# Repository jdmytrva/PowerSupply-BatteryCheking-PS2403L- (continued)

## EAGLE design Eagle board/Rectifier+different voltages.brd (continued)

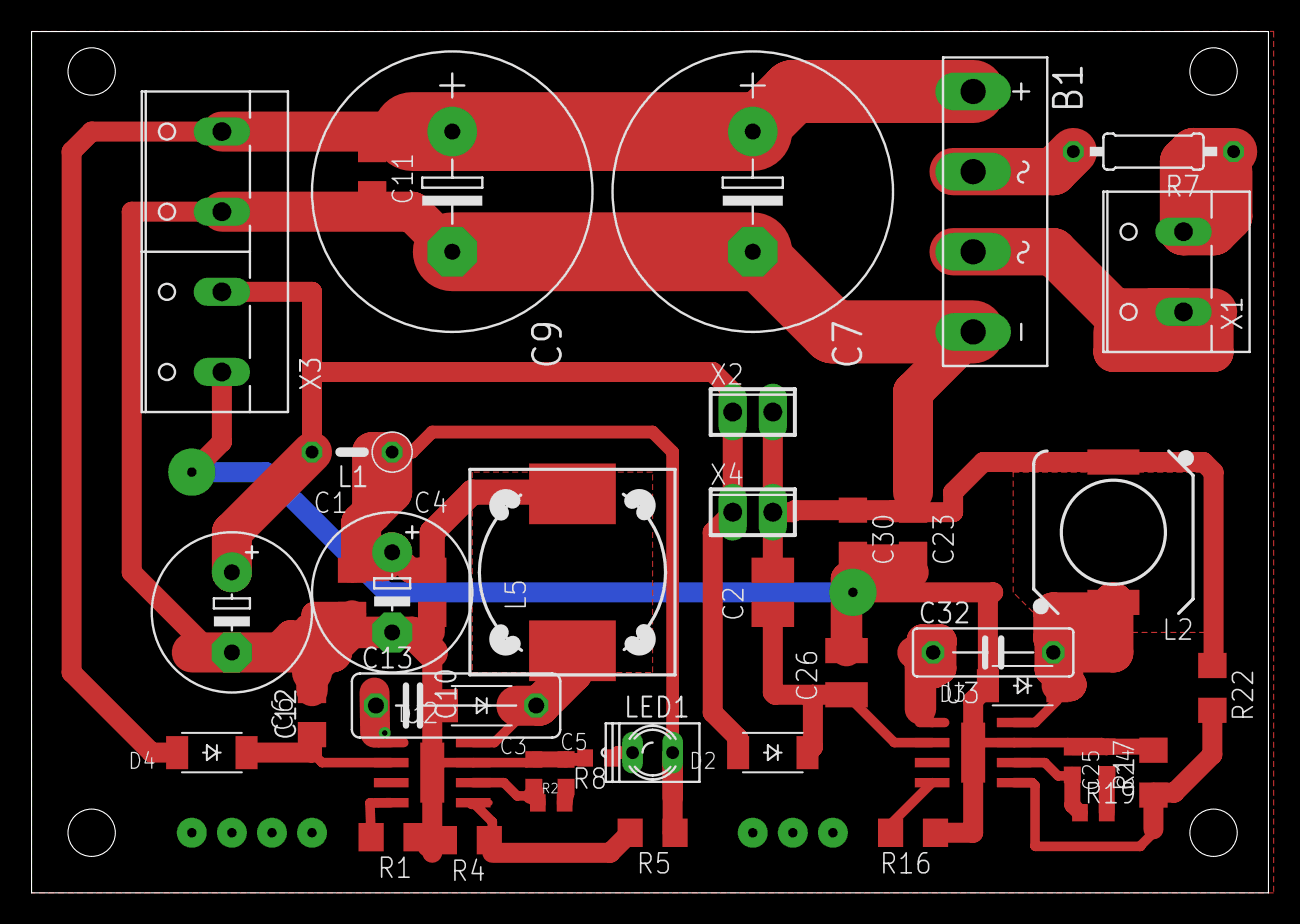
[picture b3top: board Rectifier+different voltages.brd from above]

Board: 2 copper layers, 78.4 x 54.6 mm, 43 parts (0 on the bottom side), 23 nets.

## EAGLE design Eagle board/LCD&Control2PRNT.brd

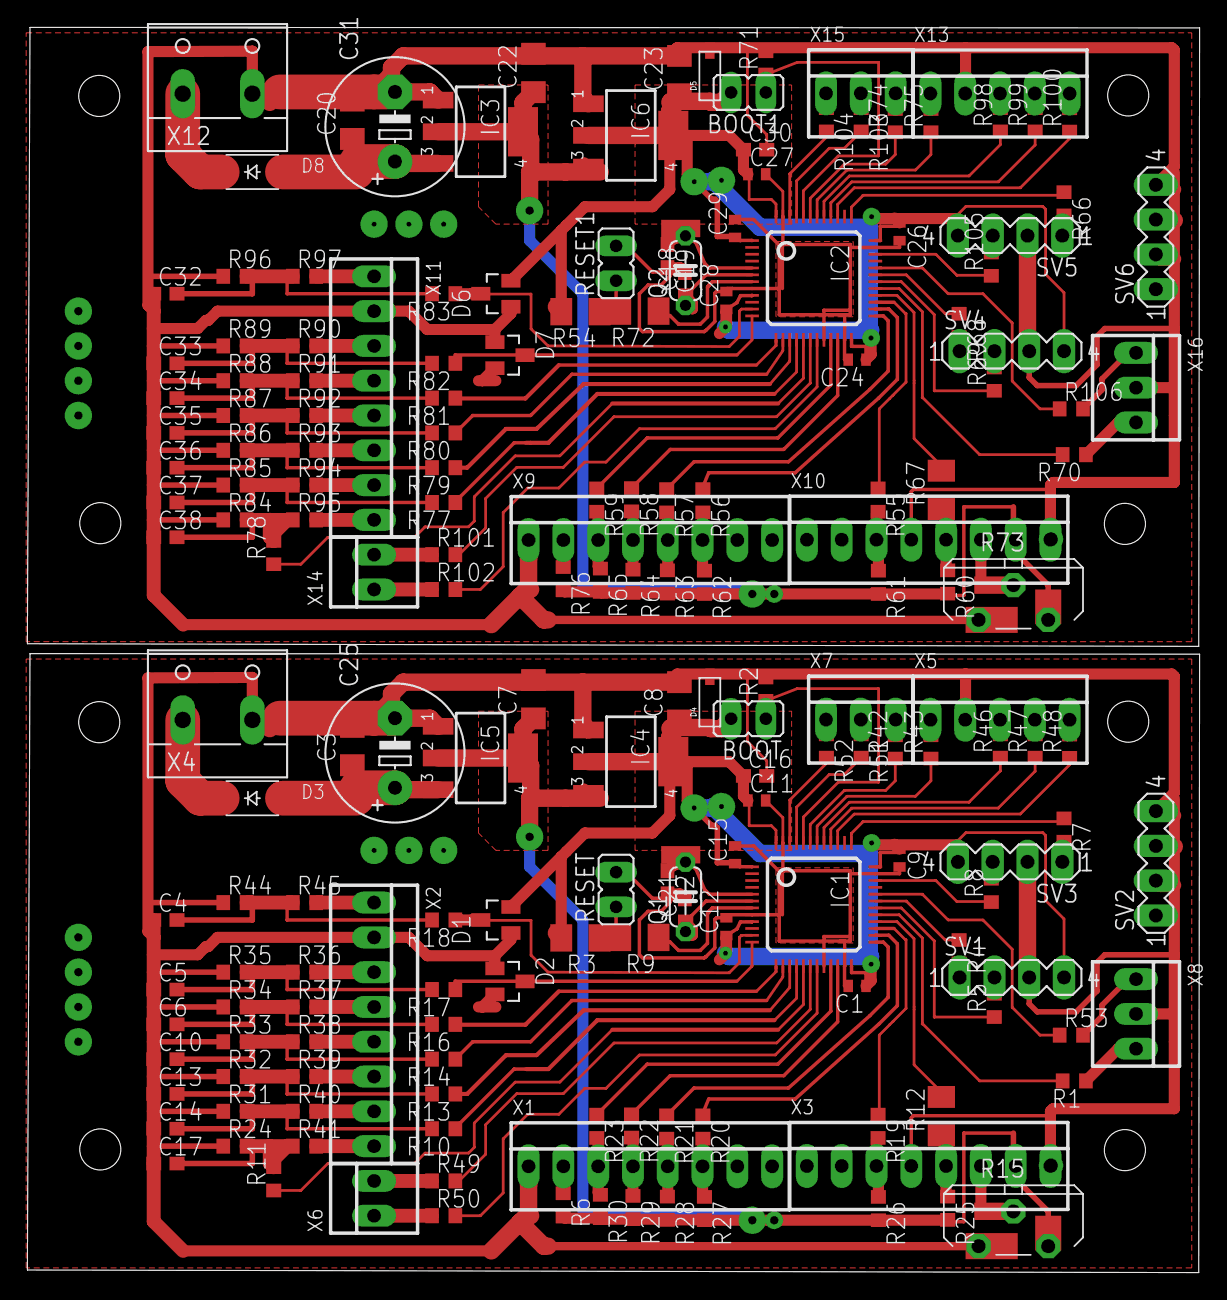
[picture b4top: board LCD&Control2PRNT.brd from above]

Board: 2 copper layers, 85.6 x 90.9 mm, 186 parts (0 on the bottom side), 150 nets.

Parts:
BOOT, BOOT1: JP1
C1, C9, C11, C12, C15, C24, C26, C27, C28, C29: 0.1; C0402
C2, C18, C19, C21: 22p; C0603
C3, C7, C8, C20, C22, C23: 0.1; C1206
C4, C5, C6, C10, C13, C14, C17, C32, C33, C34, C35, C36, C37, C38: C0603
C16, C30: 1uF; C0603
C25, C31: 470uF; E5-10,5
D1, D2, D6, D7: BAT54S; SOT23
D3, D8: PMEG4050EP; SOD128
D4, D5: 3.6v; SOD-123
IC1, IC2: STM32F10XCXT6; TQFP48
IC3, IC5: 5V; SOT223
IC4, IC6: 3.3V; SOT223
Q1, Q2: 8 Mgz; C050-024X044
R1, R4, R5, R7, R8, R10, R11, R13, R14, R16, R17, R18, R19, R24, R31, R32, R33, R34, R35, R36, R37, R38, R39, R40, R41, R42, R43, R44, R45, R46, R47, R48, R49, R50, R51, R52, R53, R55, R66, R68, R69, R70, R74, R75, R77, R78, R79, R80, R81, R82, R83, R84, R85, R86, R87, R88, R89, R90, R91, R92, R93, R94, R95, R96, R97, R98, R99, R100, R101, R102, R103, R104, R105, R106: 200; R0603
R2, R25, R26, R27, R28, R29, R30, R60, R61, R62, R63, R64, R65, R71: 10k; R0603
R3, R54: 10k; M1206
R6, R76: 470; R0603
R9, R72: 0; M1206
R12, R67: 200; M1206
R15, R73: PT-10S
R20, R21, R22, R56, R57, R58: R0603
R23, R59: 220; R0603
RESET, RESET1: JP1
SV1, SV2, SV3, SV4, SV5, SV6: MA04-1
X1, X2, X3, X9, X10, X11: 22-23-2081
X4, X12: W237-132
X5, X13: 22-23-2051
X6, X14: 22-23-2021
X7, X8, X15, X16: 22-23-2031

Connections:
+3V1: BOOT1.2, C23.1, C24.1, C26.1, C27.1, C28.1, C29.1, C30.1, D5.C, D6.2, D7.2, IC2.1, IC2.9, IC2.24, IC2.36, IC2.48, IC6.2, IC6.4, R54.2, SV4.4, SV5.4
+3V3: BOOT.2, C1.1, C8.1, C9.1, C11.1, C12.1, C15.1, C16.1, D1.2, D2.2, D4.C, IC1.1, IC1.9, IC1.24, IC1.36, IC1.48, IC4.2, IC4.4, R3.2, SV1.4, SV3.4
+5V: C7.1, IC4.3, IC5.2, IC5.4, R6.2, R15.2, R25.2, R26.2, R27.2, R28.2, R29.2, R30.2, X3.7
+5V1: C22.1, IC3.2, IC3.4, IC6.3, R60.2, R61.2, R62.2, R63.2, R64.2, R65.2, R73.2, R76.2, X10.7
+12V: C3.1, C25.+, D3.2, IC5.3
+12V1: C20.1, C31.+, D8.2, IC3.3
GND: C1.2, C2.2, C3.2, C4.1, C5.1, C6.1, C7.2, C8.2, C9.2, C10.1, C11.2, C12.2, C13.1, C14.1, C15.2, C16.2, C17.1, C21.2, C25.-, D1.1, D2.1, D4.A, IC1.8, IC1.20, IC1.23, IC1.35, IC1.47, IC4.1, IC5.1, R2.2, R15.1, R24.1, R31.1, R32.1, R33.1, R34.1, R35.1, R44.1, RESET.2, SV1.3, SV2.2, SV2.3, SV2.4, SV3.2, X1.1, X2.2, X3.4, X3.8, X4.2, X5.2, X8.2
GND1: C18.2, C19.2, C20.2, C22.2, C23.2, C24.2, C26.2, C27.2, C28.2, C29.2, C30.2, C31.-, C32.1, C33.1, C34.1, C35.1, C36.1, C37.1, C38.1, D5.A, D6.1, D7.1, IC2.8, IC2.20, IC2.23, IC2.35, IC2.47, IC3.1, IC6.1, R71.2, R73.1, R84.1, R85.1, R86.1, R87.1, R88.1, R89.1, R96.1, RESET1.2, SV4.3, SV5.2, SV6.2, SV6.3, SV6.4, X9.1, X10.4, X10.8, X11.2, X12.2, X13.2, X16.2
unnamed: IC1.29, R1.2
unnamed: C21.1, IC1.6, Q1.1
unnamed: C2.1, IC1.5, Q1.2
unnamed: IC1.37, R7.1
unnamed: IC1.34, R8.1
unnamed: R7.2, SV3.1
unnamed: R3.1, R9.2, RESET.1
unnamed: IC1.7, R9.1
unnamed: IC1.31, R4.1
unnamed: IC1.30, R5.1
unnamed: R4.2, SV1.1
unnamed: R6.1, X1.2
unnamed: R15.3, X3.6
unnamed: D3.1, X4.1
unnamed: R22.2, R29.1, X1.4
unnamed: C17.2, R11.2, R24.2, R41.1
unnamed: R52.1, X7.1
unnamed: R1.1, X8.3
unnamed: IC1.46, R52.2
unnamed: R43.2, X5.1
unnamed: R21.2, R28.1, X1.5
unnamed: D1.3, IC1.11, R18.1
unnamed: R20.2, R27.1, X1.6
unnamed: R19.2, R26.1, X3.3
unnamed: R23.2, R30.1, X1.3
unnamed: R12.1, R25.1, X3.5
unnamed: IC1.21, R23.1
unnamed: IC1.22, R22.1
unnamed: IC1.25, R21.1
unnamed: IC1.45, R51.2
unnamed: R47.2, X5.4
unnamed: R5.2, SV1.2
unnamed: R46.2, X5.3
unnamed: R48.2, X5.5
unnamed: R51.1, X7.2
unnamed: R8.2, SV3.3
unnamed: IC1.18, R49.2
unnamed: IC1.43, R42.1
unnamed: D2.3, IC1.12, R17.1
unnamed: BOOT.1, IC1.44, R2.1
unnamed: R42.2, X7.3
unnamed: IC1.42, R43.1
unnamed: C14.2, R10.2, R31.2, R40.1
unnamed: C13.2, R13.2, R32.2, R39.1
unnamed: R38.2, X2.5
unnamed: IC1.13, R16.1
unnamed: IC1.19, R50.2
unnamed: IC1.14, R14.1
unnamed: C6.2, R16.2, R34.2, R37.1
unnamed: C5.2, R17.2, R35.2, R36.1
unnamed: IC1.26, R20.1
unnamed: IC1.27, R19.1
unnamed: IC1.28, R12.2
unnamed: R49.1, X6.2
unnamed: IC1.15, R13.1
unnamed: IC1.16, R10.1
unnamed: R45.2, X2.1
unnamed: IC1.41, R46.1
unnamed: IC1.17, R11.1
unnamed: R50.1, X6.1
unnamed: IC1.40, R47.1
unnamed: IC1.39, R48.1
unnamed: C4.2, R18.2, R44.2, R45.1
unnamed: R36.2, X2.3
unnamed: R37.2, X2.4
unnamed: R53.2, X8.1
unnamed: IC1.32, R53.1
unnamed: C10.2, R14.2, R33.2, R38.1
unnamed: R39.2, X2.6
unnamed: C18.1, IC2.6, Q2.1
unnamed: C19.1, IC2.5, Q2.2
unnamed: R59.2, R65.1, X9.3
unnamed: R40.2, X2.7
unnamed: BOOT1.1, IC2.44, R71.1
unnamed: R58.2, R64.1, X9.4
unnamed: R57.2, R63.1, X9.5
unnamed: R56.2, R62.1, X9.6
unnamed: R55.2, R61.1, X10.3
unnamed: R60.1, R67.1, X10.5
unnamed: IC2.21, R59.1
unnamed: R41.2, X2.8
unnamed: IC2.22, R58.1
unnamed: IC2.25, R57.1
unnamed: IC2.26, R56.1
unnamed: IC2.27, R55.1
unnamed: IC2.28, R67.2
unnamed: IC2.34, R105.1
unnamed: IC2.31, R68.1
unnamed: IC2.30, R69.1
unnamed: R68.2, SV4.1
unnamed: R69.2, SV4.2
unnamed: R66.2, SV5.1
unnamed: IC2.37, R66.1
unnamed: R105.2, SV5.3
unnamed: R54.1, R72.2, RESET1.1
unnamed: R76.1, X9.2
unnamed: IC2.29, R70.2
unnamed: IC2.7, R72.1
unnamed: R73.3, X10.6
unnamed: D6.3, IC2.11, R83.1
unnamed: D7.3, IC2.12, R82.1
unnamed: IC2.13, R81.1
unnamed: IC2.14, R80.1
unnamed: IC2.15, R79.1
unnamed: IC2.16, R77.1
unnamed: IC2.17, R78.1
unnamed: C38.2, R78.2, R84.2, R95.1
unnamed: C37.2, R77.2, R85.2, R94.1
unnamed: C36.2, R79.2, R86.2, R93.1
unnamed: R92.2, X11.5
unnamed: C34.2, R81.2, R88.2, R91.1
unnamed: C33.2, R82.2, R89.2, R90.1
unnamed: R97.2, X11.1
unnamed: C32.2, R83.2, R96.2, R97.1
unnamed: R90.2, X11.3
unnamed: R91.2, X11.4
unnamed: C35.2, R80.2, R87.2, R92.1
unnamed: R93.2, X11.6
unnamed: R94.2, X11.7
unnamed: R95.2, X11.8
unnamed: D8.1, X12.1
unnamed: R98.2, X13.3
unnamed: R99.2, X13.4
unnamed: R100.2, X13.5
unnamed: IC2.43, R74.1
unnamed: IC2.42, R75.1
unnamed: IC2.41, R98.1
unnamed: IC2.40, R99.1
unnamed: IC2.39, R100.1
unnamed: IC2.18, R101.2
unnamed: IC2.19, R102.2
unnamed: R101.1, X14.2
unnamed: R102.1, X14.1
unnamed: IC2.46, R104.2
unnamed: IC2.45, R103.2
unnamed: IC2.32, R106.1
unnamed: R75.2, X13.1
unnamed: R104.1, X15.1
unnamed: R103.1, X15.2
unnamed: R74.2, X15.3
unnamed: R70.1, X16.3
unnamed: R106.2, X16.1

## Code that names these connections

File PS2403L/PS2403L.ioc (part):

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Mcu.Name=STM32F100C(8-B)Tx
Mcu.Package=LQFP48
Mcu.UserName=STM32F100C8Tx
PA1.Signal=ADCx_IN1
PA10.Mode=Asynchronous
PA10.Signal=USART1_RX
PA11.Signal=GPIO_Output
PA13.Mode=Serial_Wire
PA13.Signal=SYS_JTMS-SWDIO
PA14.Mode=Serial_Wire
PA14.Signal=SYS_JTCK-SWCLK
PA15.Signal=GPIO_Output
PA2.Signal=ADCx_IN2
PA3.Signal=ADCx_IN3
PA4.Signal=ADCx_IN4
PA5.Signal=ADCx_IN5
PA6.Signal=ADCx_IN6
PA8.Signal=GPIO_Output
PA9.Mode=Asynchronous
PA9.Signal=USART1_TX
PB0.Signal=GPIO_Output
PB1.Signal=GPIO_Output
PB10.GPIOParameters=GPIO_ModeDefaultOutputPP
PB10.GPIO_ModeDefaultOutputPP=GPIO_MODE_OUTPUT_OD
PB10.Signal=GPIO_Output
PB11.GPIOParameters=GPIO_ModeDefaultOutputPP
PB11.GPIO_ModeDefaultOutputPP=GPIO_MODE_OUTPUT_OD
PB11.Signal=GPIO_Output
PB12.GPIOParameters=GPIO_ModeDefaultOutputPP
PB12.GPIO_ModeDefaultOutputPP=GPIO_MODE_OUTPUT_OD
PB12.Signal=GPIO_Output
PB13.GPIOParameters=GPIO_ModeDefaultOutputPP
PB13.GPIO_ModeDefaultOutputPP=GPIO_MODE_OUTPUT_OD
PB13.Signal=GPIO_Output
PB14.GPIOParameters=GPIO_ModeDefaultOutputPP
PB14.GPIO_ModeDefaultOutputPP=GPIO_MODE_OUTPUT_OD
PB14.Signal=GPIO_Output
PB15.GPIOParameters=GPIO_ModeDefaultOutputPP
PB15.GPIO_ModeDefaultOutputPP=GPIO_MODE_OUTPUT_OD
PB15.Signal=GPIO_Output
PB4.GPIOParameters=GPIO_PuPd
PB4.GPIO_PuPd=GPIO_PULLUP
PB4.Signal=GPIO_Input
PB5.GPIOParameters=GPIO_PuPd
PB5.GPIO_PuPd=GPIO_PULLUP
PB5.Signal=GPIO_Input
PB6.GPIOParameters=GPIO_PuPd
PB6.GPIO_PuPd=GPIO_PULLUP
PB6.Signal=GPIO_Input
PB7.GPIOParameters=GPIO_PuPd
PB7.GPIO_PuPd=GPIO_PULLUP
PB7.Signal=GPIO_Input
PD0-OSC_IN.Mode=HSE-External-Oscillator
PD0-OSC_IN.Signal=RCC_OSC_IN
PD1-OSC_OUT.Mode=HSE-External-Oscillator
PD1-OSC_OUT.Signal=RCC_OSC_OUT
RCC.SYSCLKFreq_VALUE=24000000
RCC.SYSCLKSource=RCC_SYSCLKSOURCE_PLLCLK
board=custom

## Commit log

2019-05-19 fix1
2019-05-22 coproj file added
2019-06-03 PS 30V 3A v1.49
2019-06-03 PS 30V 3A v1.50
2019-06-03 PS 30V 3A v1.51
2019-06-04 PS 30V 3A v1.52 SergeyP
2019-06-04 v1.53
2019-06-04 PS 30V 3A v1.54
2019-06-04 PS 30V 3A v1.55
    Added new MenuSettingsSaveMenuPosWhenOFF
2019-06-05 PS 30V 3A v1.56
2019-06-24 PS 30V 3A v1.57
2019-06-25 PS 30V 3A v1.58
2019-06-25 PS 30V 3A v1.59
2019-06-25 PS 30V 3A v1.60
2019-07-10 v1.61. fixed swing, added attempt to read from eeprom
2019-08-08 disable eeprom write when PowerOFF
2019-08-27 Added disable irq when write/read to flash. Save C when powerOff
2019-09-07 1.64 eeprom verify
2019-09-07 1.65 fixed interrupt priority
2019-09-08 1.66 3 pages for calibration, settings, capacity
2019-09-08 1.67 Added LOG (dev phase)
2019-09-08 1.68 dev
2019-09-09 1.70 fixed EEprom Read fail
2019-09-09 1.71 log
2019-09-11 1.72 log
2019-09-12 1.73 LOG , ALSO FIXED CHARGE DISCHARGE BUGS
2019-09-17 1.74 fixed log, added charge in LOG
2019-09-27 1.75 MenuTraining_new
2019-09-27 1.76 MenuTraining_new finish
2019-09-29 1.77 Pre-Release
2019-10-28 1.79
    Added battery type
    Fixed infinity loop when off
2019-10-29 PS 23V 3A v1.80 swing+Battery type menu
2019-10-29 PS 23V 3A v1.80 swing+Battery type menu1
2019-10-30 PS 23V 3A v2.00R - PreRelease
2019-10-31 PS 23V 3A v2.00R Battery capacity menu
2019-11-01 PS 23V 3A v2.00R - for tests
2019-11-04 PS 24V 3A v2.01R - adeed DELTA_UPS_BAT_MAX 5 //50mv
2019-11-08 PS 24V3.5A v2.02 FAN
2019-11-29 PS 24V3.5A v2.10 - added Key UP, Removed FAN
2019-11-29 PS 24V3.5A v2.10 - added Key UP, Removed FAN
2019-11-29 removed Eagle board
2020-01-21 PS 22V2.5A v2.11
2020-01-21 2 Line LCD
2020-02-12 fixed calibration values
2020-02-12 PS 22V2.5A v2.20 - added option "OUT after powerUp"
2020-02-13 timers
2020-02-14 Delay with systick
2020-02-14 buzzer
2020-02-27 PS 22V2.5A v2.30 MenuBatterySimilation
2020-03-07 PS 22V2.5A v2.40 added temperature of PowerBoard
2020-03-08 PS 22V2.5A v2.40. OFf when Temperature more then 85C
2020-03-09 PS+L 20V3A v2.41 - fix out of memory
2020-08-28 v2.42 - fixed bugs. Passed smoke tests
2020-11-09 PS+L 20V3A v2.50 - new filter. STM32CubeIDE
2020-11-09 cosmetics changes
2020-11-12 Added hex of working version
2020-11-25 v2.60 - fixed bugs. Passed smoke tests
2021-02-18 PS+L 20V3A v2.61 - fixed stuck
    while (bufferUart1.tx_counter >= TX_BUFFER_SIZE-30); //если буфер переполнен, ждем
